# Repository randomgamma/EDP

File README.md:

Experiment 1-: Receiver(Rx)
Experiment 2-: IR
Experiment 3-: Transmitter(Tx)

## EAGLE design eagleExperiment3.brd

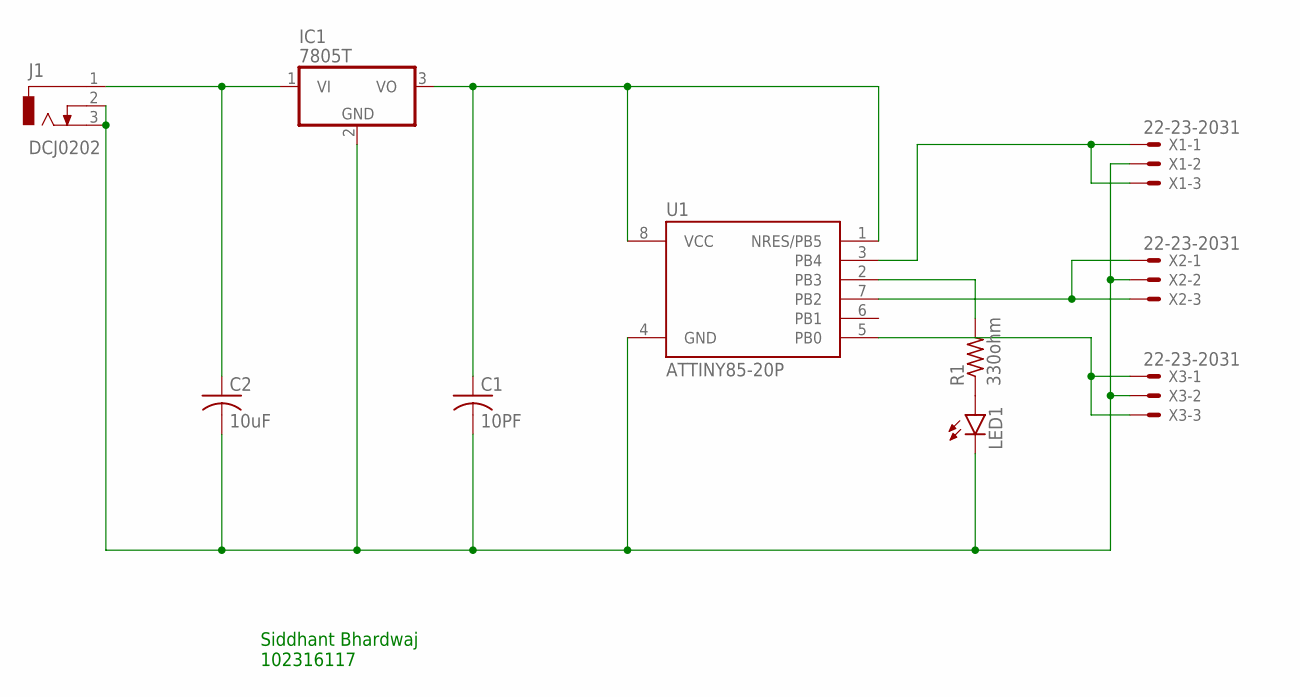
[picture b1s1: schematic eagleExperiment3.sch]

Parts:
C1: 10PF; C025-024X044
C2: 10uF; C025-024X044
IC1: 7805T; TO220H
J1: DCJ0202
LED1: LED3MM
R1: 330ohm; 0207/5V
U1: ATTINY85-20P; PDIP08_300MIL
X1, X2, X3: 22-23-2031

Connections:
unnamed: U1.3 (PB4), X1.1, X1.3
unnamed: C1.2, C2.2, IC1.2 (GND), J1.2, J1.3, LED1.K (C), U1.4 (GND), X1.2, X2.2, X3.2
unnamed: C2.1, IC1.1 (VI), J1.1
unnamed: C1.1, IC1.3 (VO), U1.1 (NRES/PB5), U1.8 (VCC)
unnamed: LED1.A, R1.1
unnamed: R1.2, U1.2 (PB3)
unnamed: U1.5 (PB0), X3.1, X3.3
unnamed: U1.7 (PB2), X2.1, X2.3

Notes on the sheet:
Siddhant Bhardwaj 102316117

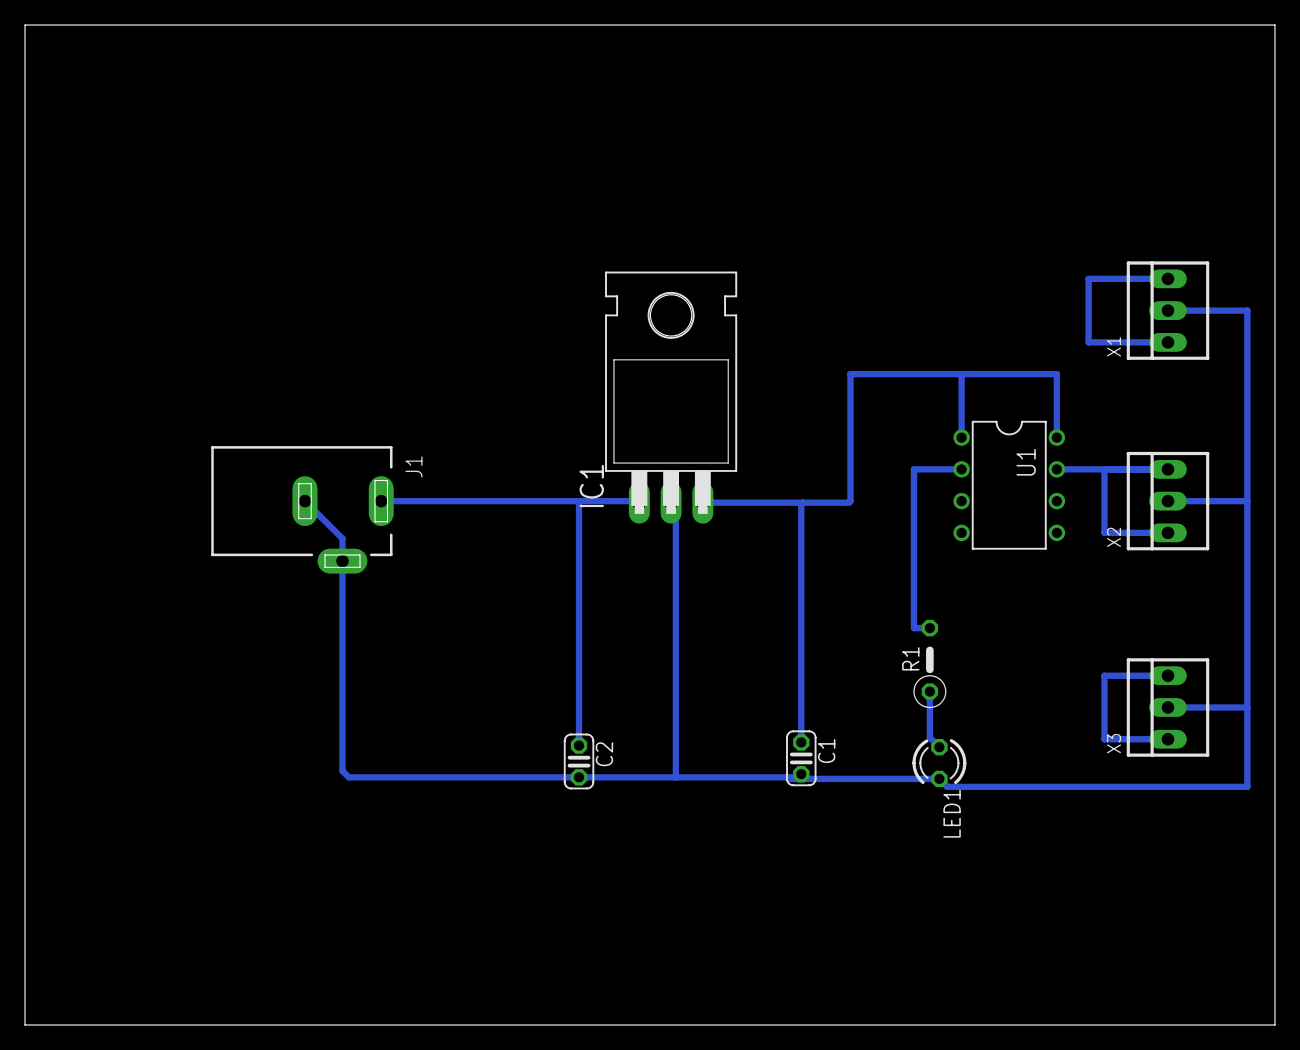
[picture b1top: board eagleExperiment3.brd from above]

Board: 2 copper layers, 100.0 x 80.0 mm, 10 parts (0 on the bottom side), 8 nets.

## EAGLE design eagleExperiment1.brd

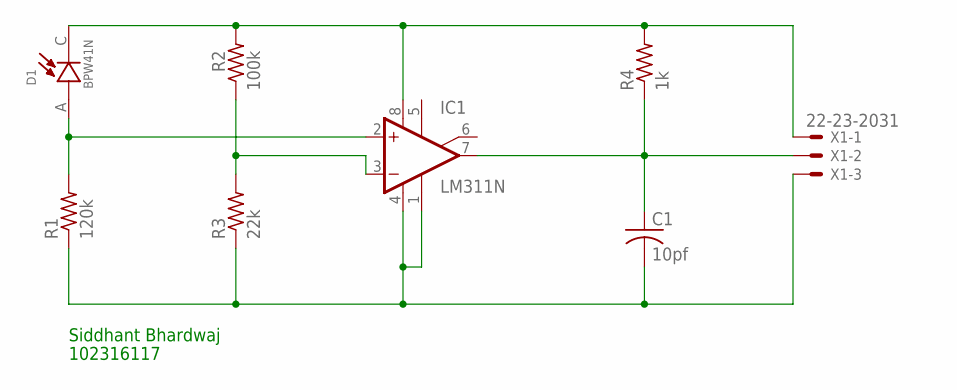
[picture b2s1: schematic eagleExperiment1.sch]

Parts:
C1: 10pf; C025-025X050
D1: BPW41N; DIO_BPW41N
IC1: LM311N; DIL08
R1: 120k; 0204/5
R2: 100k; 0204/5
R3: 22k; 0204/5
R4: 1k; 0204/5
X1: 22-23-2031

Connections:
unnamed: D1.A, IC1.2 (+IN), R1.2
unnamed: IC1.3 (-IN), R2.1, R3.2
unnamed: C1.1, IC1.7 (OUT), R4.1, X1.2
unnamed: D1.C, IC1.8 (V+), R2.2, R4.2, X1.1
unnamed: C1.2, IC1.1 (GND), IC1.4 (V-), R1.1, R3.1, X1.3

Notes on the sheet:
Siddhant Bhardwaj
102316117

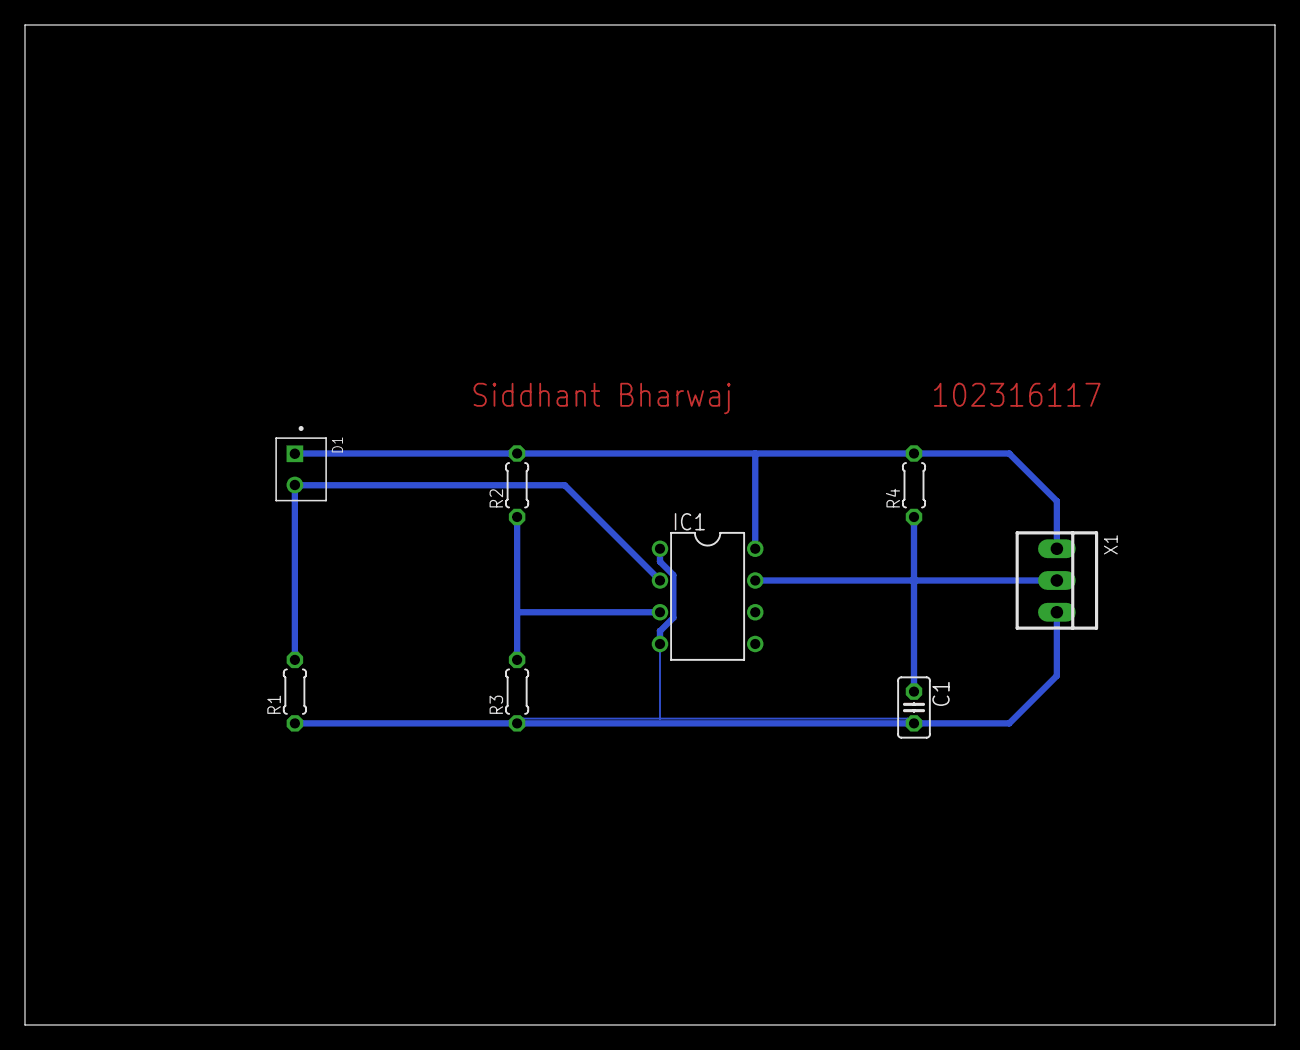
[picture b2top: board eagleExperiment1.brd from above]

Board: 2 copper layers, 100.0 x 80.0 mm, 8 parts (0 on the bottom side), 5 nets.

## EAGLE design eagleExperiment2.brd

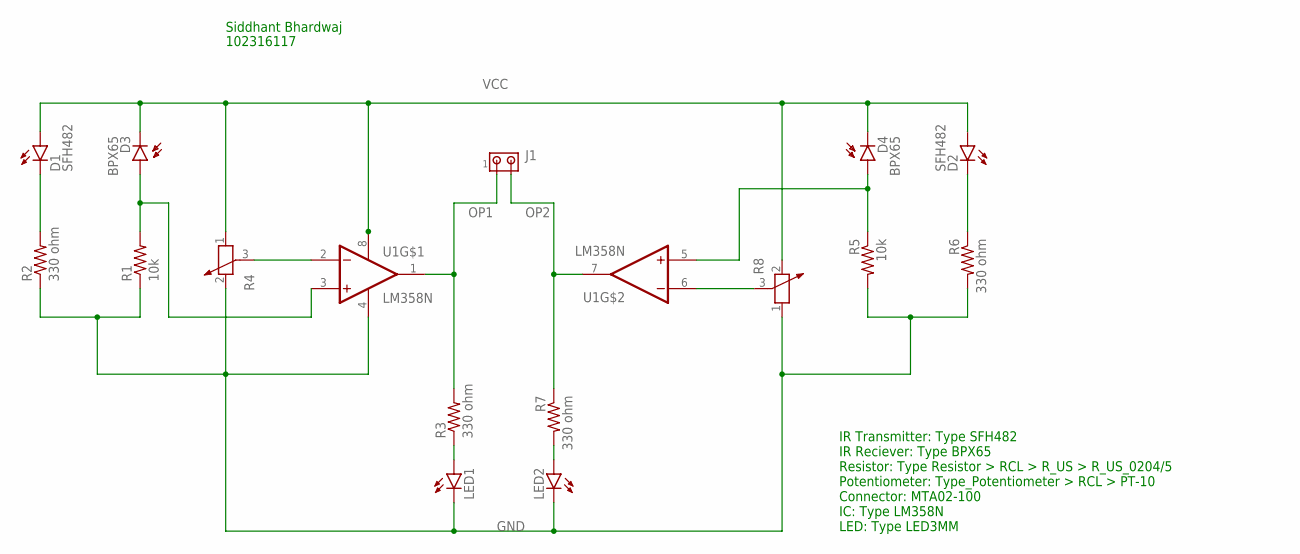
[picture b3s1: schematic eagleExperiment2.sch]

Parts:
D1, D2: SFH482
D3, D4: BPX65
J1: MTA02-100; 10X02MTA
LED1, LED2: LED3MM
R1, R5: 10k; 0204/5
R2, R3, R6, R7: 330 ohm; 0204/5
R4, R8: POTENTIOMETER_PT-10; PT-10
U1: LM358N; DIP762W46P254L960H508Q8

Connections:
GND: LED1.K (C), LED2.K (C), R1.1, R2.1, R4.2, R5.2, R6.2, R8.1, U1.4 (GND)
unnamed: LED1.A, R3.1
unnamed: D3.A, R1.2, U1.3 (1IN+)
unnamed: R4.3, U1.2 (1IN-)
unnamed: D1.K (C), R2.2
unnamed: LED2.A, R7.2
unnamed: R8.3, U1.6 (2IN-)
unnamed: D2.K (C), R6.1
unnamed: D4.A, R5.1, U1.5 (2IN+)
OP1: J1.1, R3.2, U1.1 (1OUT)
OP2: J1.2, R7.1, U1.7 (2OUT)
VCC: D1.A, D2.A, D3.K (C), D4.K (C), R4.1, R8.2, U1.8 (VCC)

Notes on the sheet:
Siddhant Bhardwaj
102316117
IR Transmitter: Type SFH482 IR Reciever: Type BPX65 Resistor: Type Resistor > RCL > R_US > R_US_0204/5 Potentiometer: Type_Potentiometer > RCL > PT-10 Connector: MTA02-100 IC: Type LM358N LED: Type LED3MM

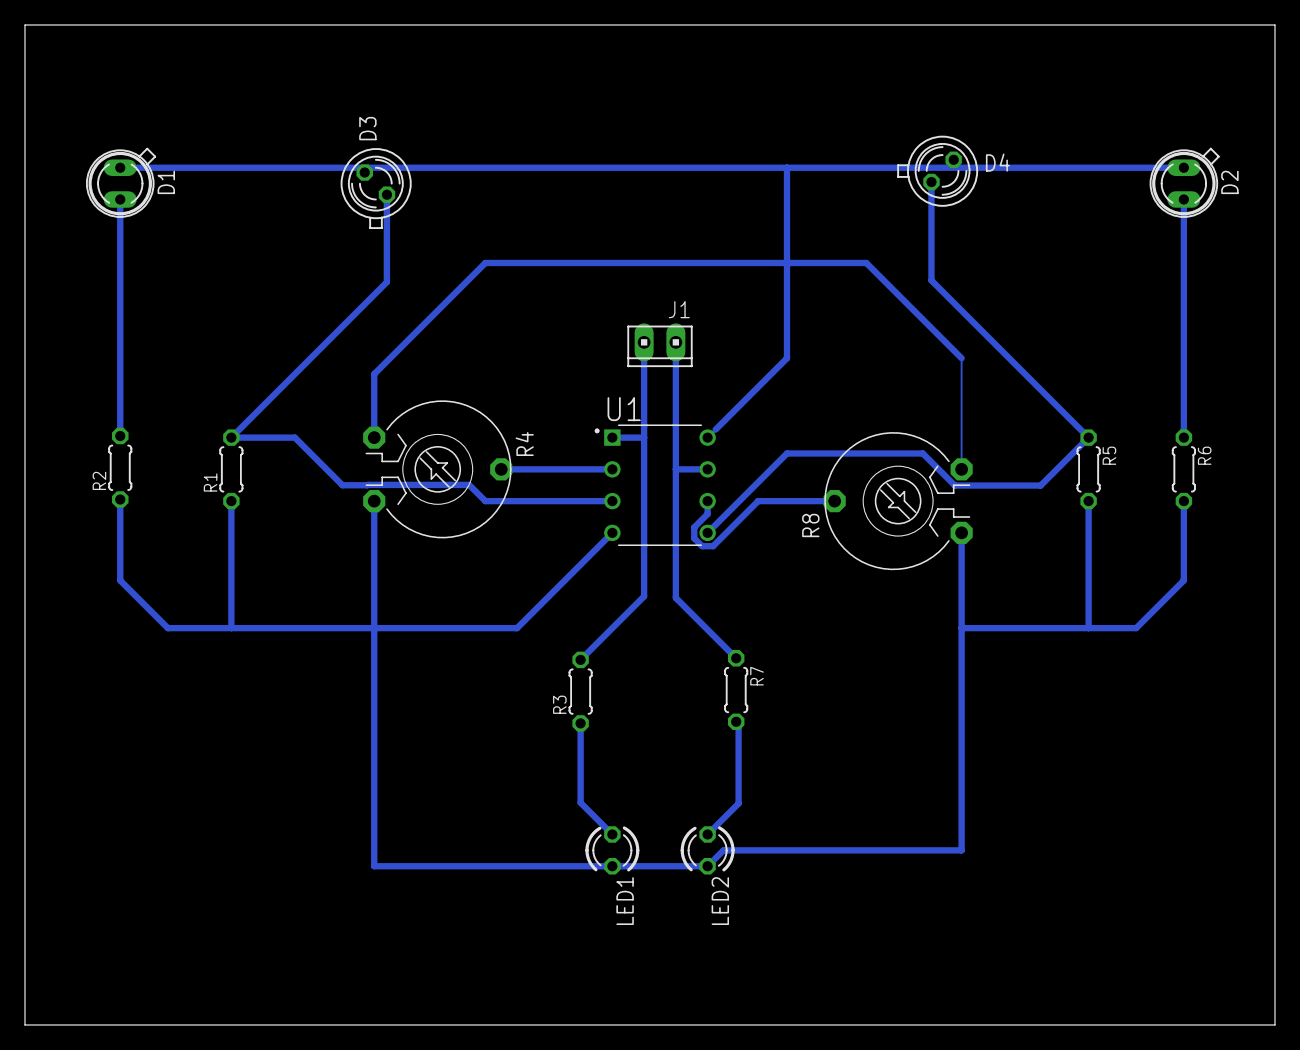
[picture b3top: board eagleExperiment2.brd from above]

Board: 2 copper layers, 100.0 x 80.0 mm, 16 parts (0 on the bottom side), 12 nets.
